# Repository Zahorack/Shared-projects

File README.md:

# Shared-projects
This repository contains some of my older simple non commercial projects.

# List of projects

* [Wheel speed encoder](https://github.com/Zahorack/embedded-open-projects/tree/master/SpeedEncoder)
<p align="left">

* [HMR_02 homemade low-cost sonar](https://github.com/Zahorack/embedded-open-projects/tree/master/HMR-02)
<p align="left">

* [Long Range IoT module](https://github.com/Zahorack/Shared-projects/blob/master/LongRangeIoTModule)
<p align="left">

* [MultiController](https://github.com/Zahorack/Shared-projects/blob/master/MultiController)
<p align="left">

* [SunTracker](https://github.com/Zahorack/Shared-projects/blob/master/Suntracker)
<p align="left">

* [GoldFish](https://github.com/Zahorack/Shared-projects/tree/master/GoldFish)
<p align="left">

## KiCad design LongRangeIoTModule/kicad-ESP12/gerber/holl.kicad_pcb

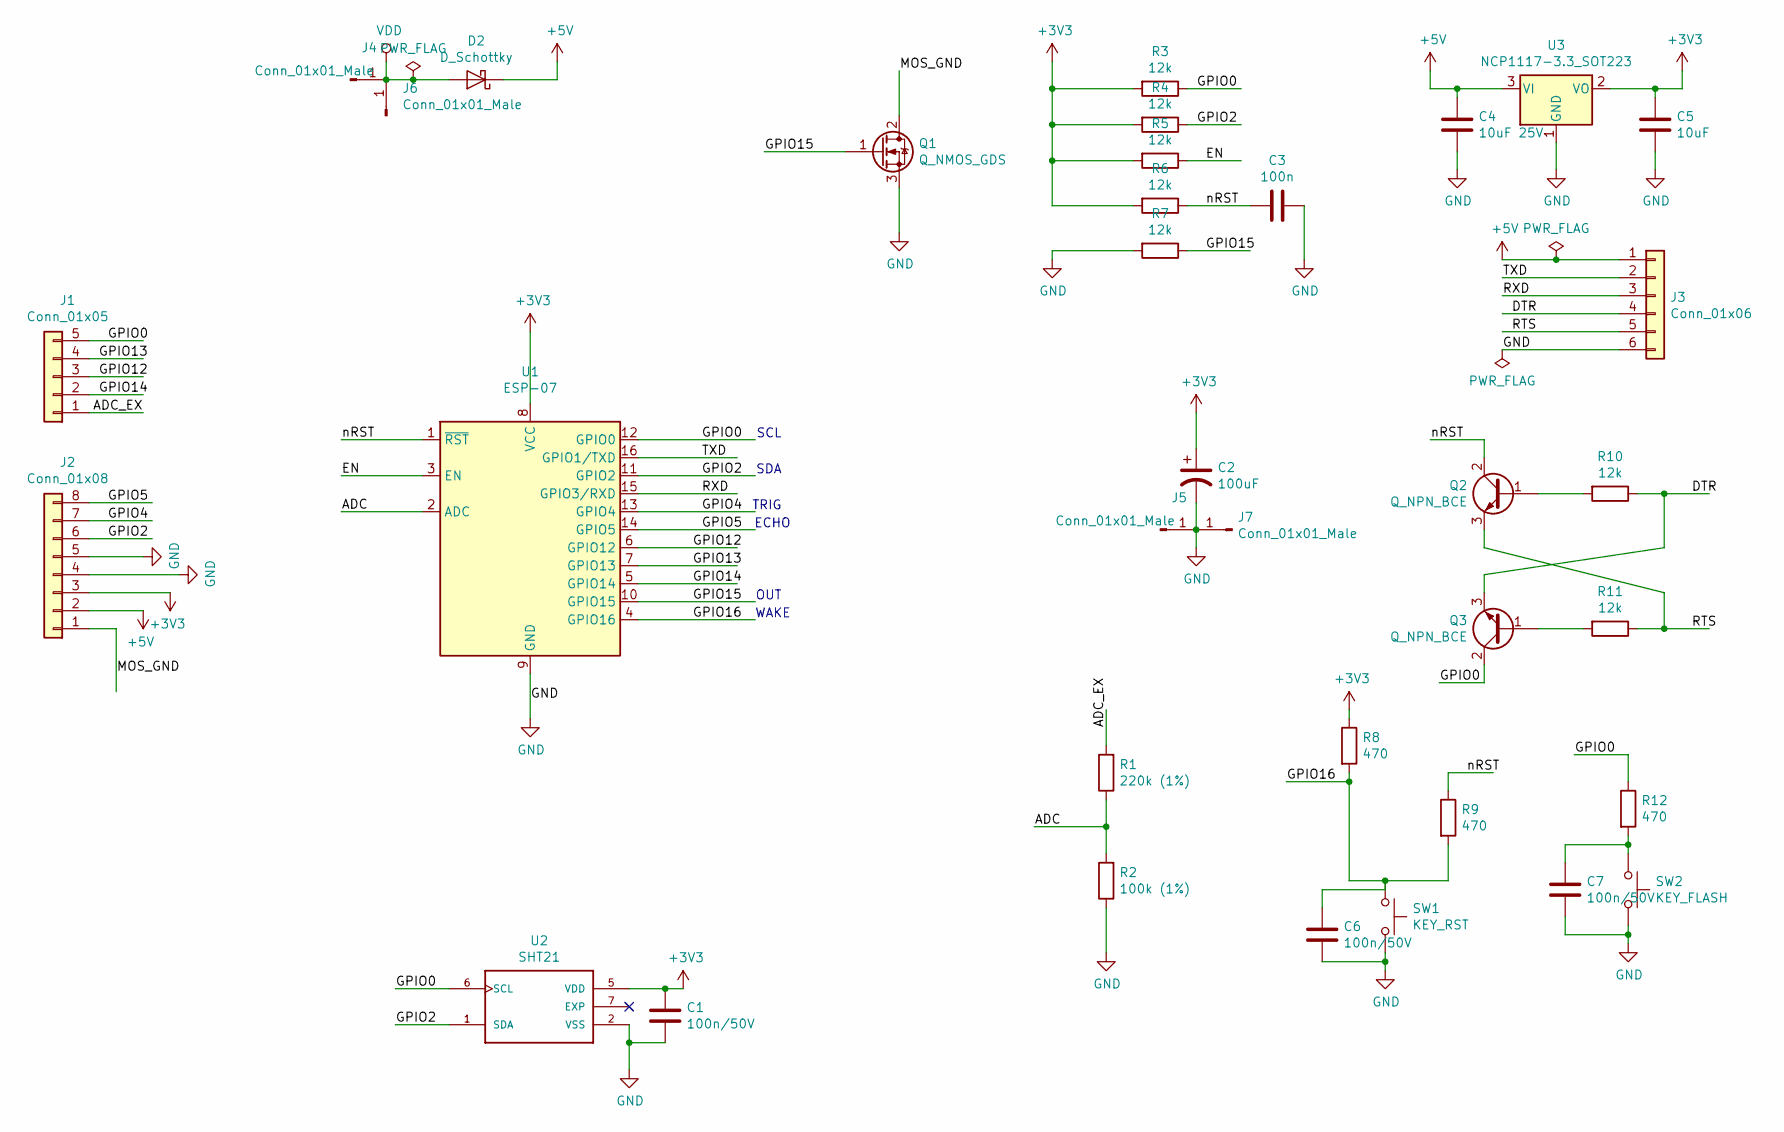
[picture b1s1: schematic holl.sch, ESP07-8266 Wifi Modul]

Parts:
C1, C6, C7: 100n/50V; C_0603_1608Metric_Pad1.05x0.95mm_HandSolder
C2: 100uF; CP_EIA-7343-31_Kemet-D_Pad2.25x2.55mm_HandSolder
C3: 100n; C_0603_1608Metric_Pad1.05x0.95mm_HandSolder
C4: 10uF 25V; C_0805_2012Metric_Pad1.15x1.40mm_HandSolder
C5: 10uF; C_0805_2012Metric_Pad1.15x1.40mm_HandSolder
D2: D_Schottky; D_SOD-123
J1: Conn_01x05; PinSocket_1x05_P2.54mm_Vertical
J2: Conn_01x08; PinSocket_1x08_P2.54mm_Vertical
J3: Conn_01x06; PinSocket_1x06_P2.54mm_Vertical
J4, J5: Conn_01x01_Male; PinHeader_1x01_P2.54mm_Vertical
J6, J7: Conn_01x01_Male; TestPoint_Pad_2.0x2.0mm
Q1: Q_NMOS_GDS; SOT-23
Q2, Q3: Q_NPN_BCE; SOT-23
R1: 220k (1%); R_0603_1608Metric
R2: 100k (1%); R_0603_1608Metric
R3, R4, R5, R6, R7, R10, R11: 12k; R_0603_1608Metric
R8, R9, R12: 470; R_0603_1608Metric
SW1: KEY_RST; SW_SPST_CK_RS282G05A3
SW2: KEY_FLASH; SW_SPST_CK_RS282G05A3
U1: ESP-07; ESP-07_1
U2: SHT21; nove
U3: NCP1117-3.3_SOT223; SOT-223-3_TabPin2

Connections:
+3V3: C1.1, C2.1, C5.1, J2.3, R3.2, R4.2, R5.2, R6.2, R8.1, U1.8 (VCC), U2.5 (VDD), U3.2 (VO)
+5V: C4.1, D2.1 (K), J2.2, J3.1, U3.3 (VI)
/ADC: R1.1, R2.2, U1.2 (ADC)
/ADC_EX: J1.1, R1.2
/DTR: J3.4, Q3.3 (E), R10.1
/EN: R5.1, U1.3 (EN)
/GPIO0: J1.5, Q3.2 (C), R3.1, R12.1, U1.12 (GPIO0), U2.6 (SCL)
/GPIO2: J2.6, R4.1, U1.11 (GPIO2), U2.1 (SDA)
/GPIO4: J2.7, U1.13 (GPIO4)
/GPIO5: J2.8, U1.14 (GPIO5)
/GPIO12: J1.3, U1.6 (GPIO12)
/GPIO13: J1.4, U1.7 (GPIO13)
/GPIO14: J1.2, U1.5 (GPIO14)
/GPIO15: Q1.1 (G), R7.1, U1.10 (GPIO15)
/GPIO16: C6.1, R8.2, R9.2, SW1.1, U1.4 (GPIO16)
/MOS_GND: J2.1, Q1.2 (D)
/RTS: J3.5, Q2.3 (E), R11.1
/RXD: J3.3, U1.15 (GPIO3/RXD)
/TXD: J3.2, U1.16 (GPIO1/TXD)
/nRST: C3.2, Q2.2 (C), R6.1, R9.1, U1.1 (~RST)
GND: C1.2, C2.2, C3.1, C4.2, C5.2, C6.2, C7.2, J2.4, J2.5, J3.6, J5.1, J7.1, Q1.3 (S), R2.1, R7.2, SW1.2, SW2.2, U1.9 (GND), U2.2 (VSS), U3.1 (GND)
unnamed: C7.1, R12.2, SW2.1
unnamed: Q2.1 (B), R10.2
unnamed: Q3.1 (B), R11.2
VDD: D2.2 (A), J4.1, J6.1

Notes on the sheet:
TRIG
ECHO
SDA
SCL
OUT
WAKE

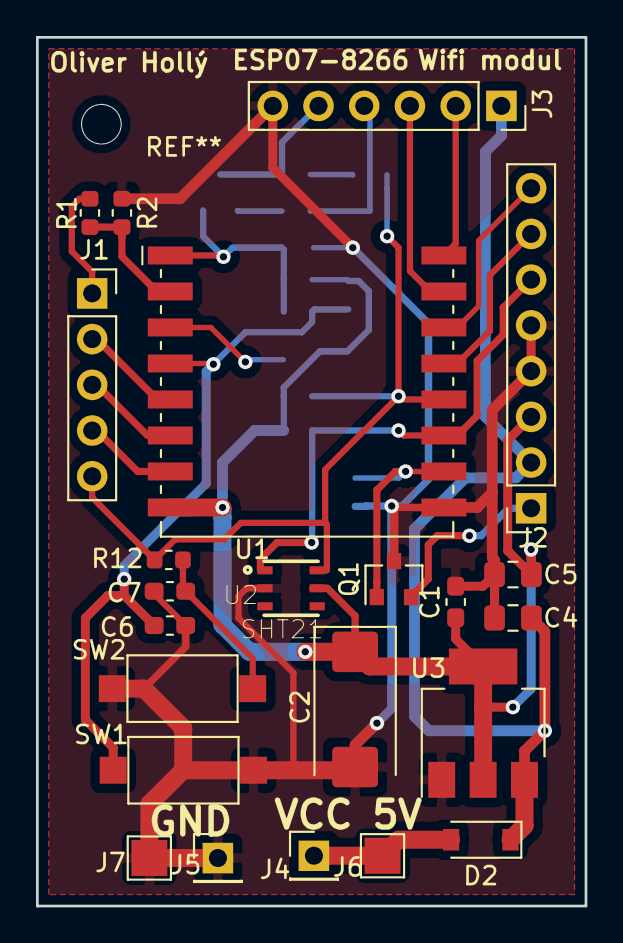
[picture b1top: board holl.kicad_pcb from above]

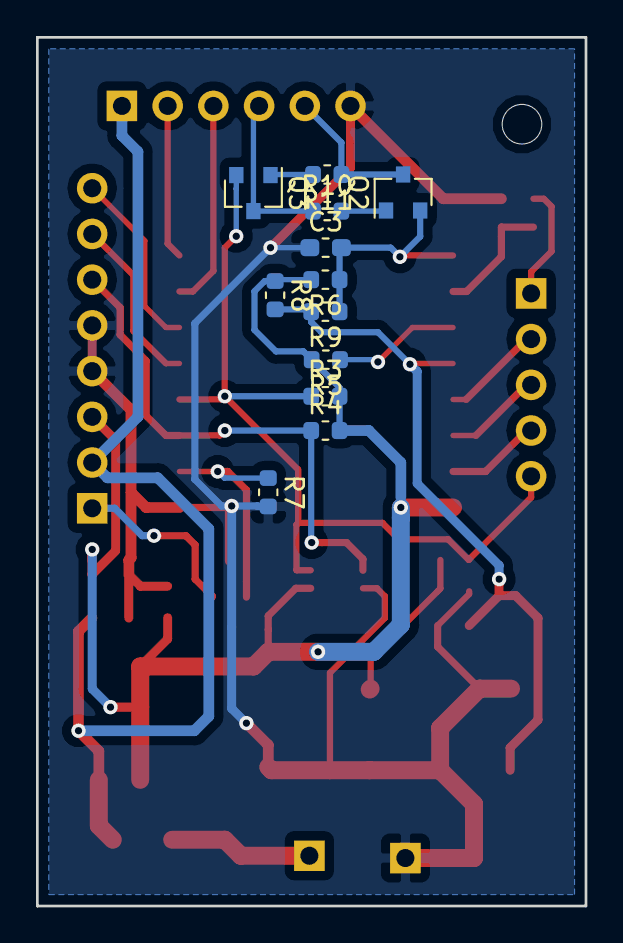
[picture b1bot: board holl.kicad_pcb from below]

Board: 2 copper layers, 30.5 x 48.3 mm, 35 parts (12 on the bottom side), 25 nets.

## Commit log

2019-01-17 add readme
2019-01-18 commit test
2019-01-18 commit test 3
2019-01-18 multicontroller readme
2019-01-19 mulltincontroller schematic
2019-01-20 add Suntracker project
2019-01-20 rotete image
2019-01-20 remove part
2019-01-20 rotate image
2019-01-20 rotate image 2
2019-01-20 add suntracker schematic
2019-01-20 add source files
2019-01-26 Added GoldFish new project
2019-01-26 Added GoldFish image
2019-10-30 Add rc pwm control
2020-03-17 Add long range iot module project
2020-03-17 Add long range iot module photodocumentaion
2020-03-24 Add Voltage rugulator simulation
2020-05-05 Add HMR_02 and Speed Encoder project
2020-05-05 HMR02 rename imgs
